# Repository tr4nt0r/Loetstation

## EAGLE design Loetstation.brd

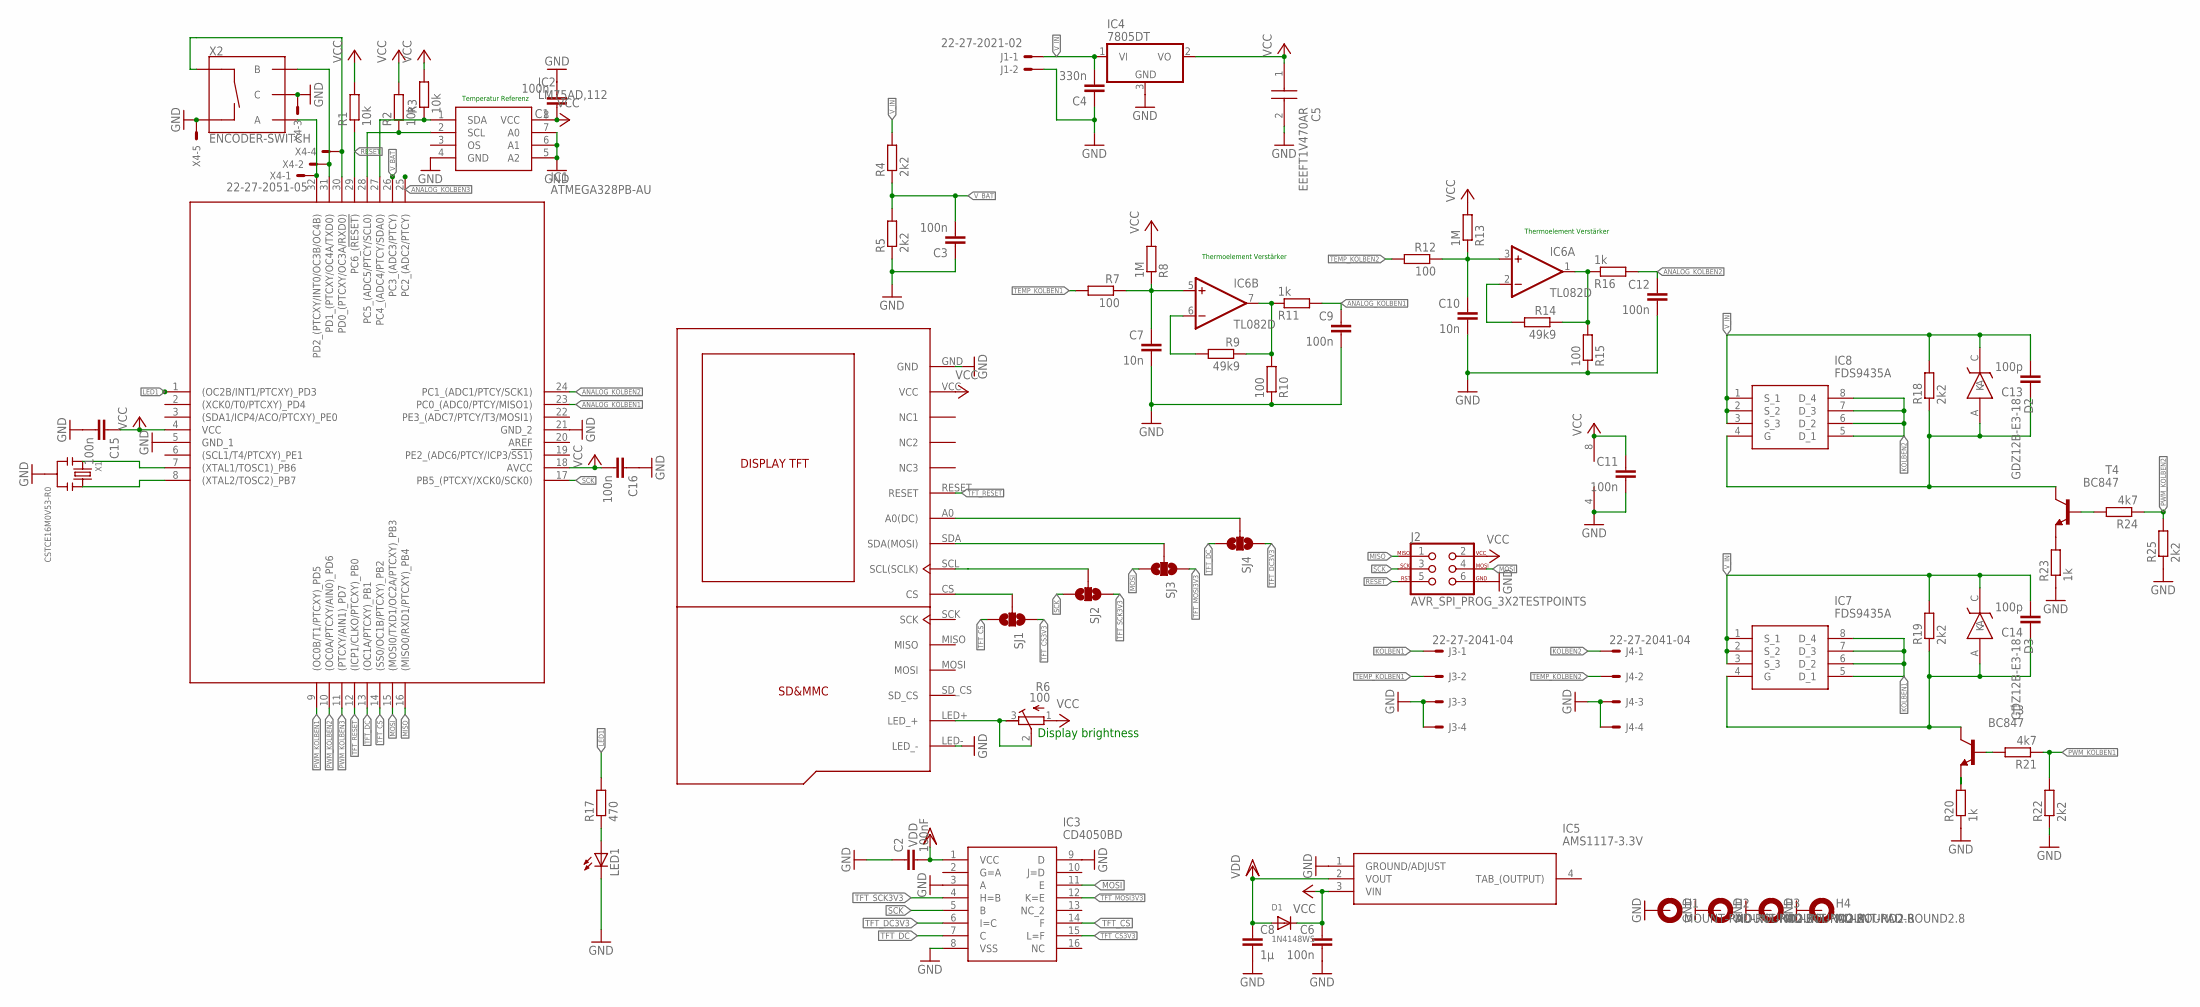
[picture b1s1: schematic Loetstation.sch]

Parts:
C1, C3, C6, C9, C11, C12, C15, C16: 100n; C0603
C2: 100nF; C0603
C4: 330n; C0603
C5: EEEFT1V470AR; EEEFT(C)
C7, C10: 10n; C0603
C8: 1µ; C0603
C13, C14: 100p; C0603
D1: 1N4148WS; SOD-323F
D2, D3: GDZ12B-E3-18; SOD323-W
H1, H2, H3, H4: MOUNT-PAD-ROUND2.8; 2,8-PAD
IC1: ATMEGA328PB-AU; QFP80P900X900X120-32N
IC2: LM75AD,112; SOIC127P600X175-8N
IC3: CD4050BD; SOIC127P600X175-16N
IC4: 7805DT; TO252
IC5: AMS1117-3.3V; SOT229P700X180-4N
IC6: TL082D; SO08
IC7, IC8: FDS9435A; SOIC127P600X175-8N
J1: 22-27-2021-02; 6410-02
J2: AVR_SPI_PROG_3X2TESTPOINTS; 2X3_TEST_POINTS
J3, J4: 22-27-2041-04; 6410-04
LED1: LEDCHIPLED_0805; CHIPLED_0805
R1, R2, R3: 10k; R0402
R4, R5, R18, R19, R22, R25: 2k2; R0402
R6: 100; EVM-3ESX50B
R7, R10, R12, R15: 100; R0402
R8, R13: 1M; R0402
R9, R14: 49k9; R0402
R11, R16, R20, R23: 1k; R0402
R17: 470; R0402
R21, R24: 4k7; R0402
SJ1, SJ2, SJ3, SJ4: SOLDERJUMPER_2WAYS; SJ_3
T3, T4: BC847; SOT23
X1: CSTCE16M0V53-R0; CSTCE-V
X3: DISPLAY_TFT_1,8; DISPLAY_TFT_1,8-KMR
X4: 22-27-2051-05; 6410-05

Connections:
ANALOG_KOLBEN1: C9.1, IC1.23 (PC0_(ADC0/PTCY/MISO1)), R11.2
ANALOG_KOLBEN2: C12.1, IC1.24 (PC1_(ADC1/PTCY/SCK1)), R16.2
ANALOG_KOLBEN3: IC1.25 (PC2_(ADC2/PTCY))
GND: C1.2, C2.1, C3.1, C4.1, C5.2 (+), C6.2, C7.2, C8.2, C9.2, C10.2, C11.2, C12.2, C15.2, C16.1, H1.B2,8, H2.B2,8, H3.B2,8, H4.B2,8, IC1.5 (GND_1), IC1.21 (GND_2), IC2.4 (GND), IC2.5 (A2), IC2.6 (A1), IC2.7 (A0), IC3.3 (A), IC3.8 (VSS), IC3.9 (D), IC4.3 (GND), IC5.1 (GROUND/ADJUST), IC6.4 (V-), J1.2, J2.6, J3.3, J3.4, J4.3, J4.4, LED1.C, R5.1, R10.1, R15.1, R20.1, R22.1, R23.1, R25.1, X1.2, X3.GND, X3.LED- (LED_-), X4.3, X4.5
KOLBEN1: IC7.5 (D_1), IC7.6 (D_2), IC7.7 (D_3), IC7.8 (D_4), J3.1
KOLBEN2: IC8.5 (D_1), IC8.6 (D_2), IC8.7 (D_3), IC8.8 (D_4), J4.1
LED1: IC1.1 ((OC2B/INT1/PTCXY)_PD3), R17.2
MISO: IC1.16 ((MISO0/RXD1/PTCXY)_PB4), J2.1
MOSI: IC1.15 ((MOSI0/TXD1/OC2A/PTCXY)_PB3), IC3.11 (E), J2.4, SJ3.3
unnamed: SJ4.2, X3.A0 (A0(DC))
unnamed: SJ3.2, X3.SDA (SDA(MOSI))
unnamed: C13.1, D2.A, IC8.4 (G), R18.1, T4.3 (C)
unnamed: C14.1, D3.A, IC7.4 (G), R19.1, T3.3 (C)
unnamed: R24.2, T4.1 (B)
unnamed: R23.2, T4.2 (E)
unnamed: IC6.7 (OUT), R9.1, R10.2, R11.1
unnamed: R21.2, T3.1 (B)
unnamed: R20.2, T3.2 (E)
unnamed: C7.1, IC6.5 (+IN), R7.1, R8.1
unnamed: IC1.7 ((XTAL1/TOSC1)_PB6), X1.1
unnamed: IC1.8 ((XTAL2/TOSC2)_PB7), X1.3
unnamed: IC1.28 (PC5_(ADC5/PTCY/SCL0)), IC2.2 (SCL), R2.1
unnamed: IC1.27 (PC4_(ADC4/PTCY/SDA0)), IC2.1 (SDA), R3.1
unnamed: SJ2.2, X3.SCL (SCL(SCLK))
unnamed: SJ1.2, X3.CS
unnamed: IC6.6 (-IN), R9.2
unnamed: C10.1, IC6.3 (+IN), R12.1, R13.1
unnamed: LED1.A, R17.1
unnamed: IC1.32 (PD2_(PTCXY/INT0/OC3B/OC4B)), X4.1
unnamed: IC1.31 (PD1_(PTCXY/OC4A/TXD0)), X4.2
unnamed: IC1.30 (PD0_(PTCXY/OC3A/RXD0)), X4.4
unnamed: R6.2 (S), R6.3 (E), X3.LED+ (LED_+)
unnamed: IC6.1 (OUT), R14.1, R15.2, R16.1
unnamed: IC6.2 (-IN), R14.2
PWM_KOLBEN1: IC1.9 ((OC0B/T1/PTCXY)_PD5), R21.1, R22.2
PWM_KOLBEN2: IC1.10 ((OC0A/PTCXY/AIN0)_PD6), R24.1, R25.2
PWM_KOLBEN3: IC1.11 ((PTCXY/AIN1)_PD7)
RESET: IC1.29 (PC6_(!RESET)), J2.5, R1.1
SCK: IC1.17 (PB5_(PTCXY/XCK0/SCK0)), IC3.5 (B), J2.3, SJ2.3
TEMP_KOLBEN1: J3.2, R7.2
TEMP_KOLBEN2: J4.2, R12.2
TFT_CS: IC1.14 ((SS0/OC1B/PTCXY)_PB2), IC3.14 (F), SJ1.3
TFT_CS3V3: IC3.15 (L=F), SJ1.1
TFT_DC: IC1.13 ((OC1A/PTCXY)_PB1), IC3.7 (C), SJ4.3
TFT_DC3V3: IC3.6 (I=C), SJ4.1
TFT_MOSI3V3: IC3.12 (K=E), SJ3.1
TFT_RESET: IC1.12 ((ICP1/CLKO/PTCXY)_PB0), X3.RESET
TFT_SCK3V3: IC3.4 (H=B), SJ2.1
VCC: C1.1, C5.1 (-), C6.1, C11.1, C15.1, C16.2, D1.C, IC1.4 (VCC), IC1.18 (AVCC), IC2.8 (VCC), IC4.2 (VO), IC5.3 (VIN), IC6.8 (V+), J2.2, R1.2, R2.2, R3.2, R6.1 (A), R8.2, R13.2, X3.VCC
VDD: C2.2, C8.1, D1.A, IC3.1 (VCC), IC5.2 (VOUT)
V_BAT: C3.2, IC1.26 (PC3_(ADC3/PTCY)), R4.1, R5.2
V_IN: C4.2, C13.2, C14.2, D2.C (K), D3.C (K), IC4.1 (VI), IC7.1 (S_1), IC7.2 (S_2), IC7.3 (S_3), IC8.1 (S_1), IC8.2 (S_2), IC8.3 (S_3), J1.1, R4.2, R18.2, R19.2

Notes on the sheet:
Display brightness
Temperatur Referenz
Thermoelement Verstärker

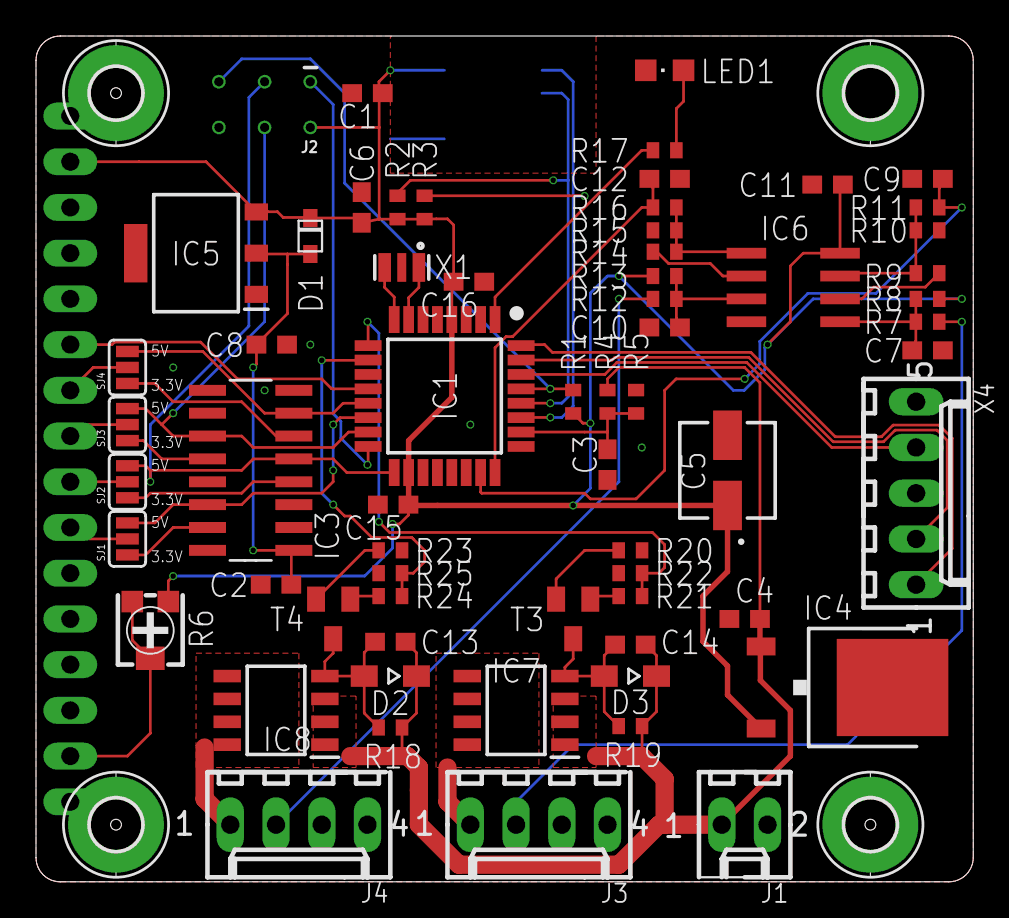
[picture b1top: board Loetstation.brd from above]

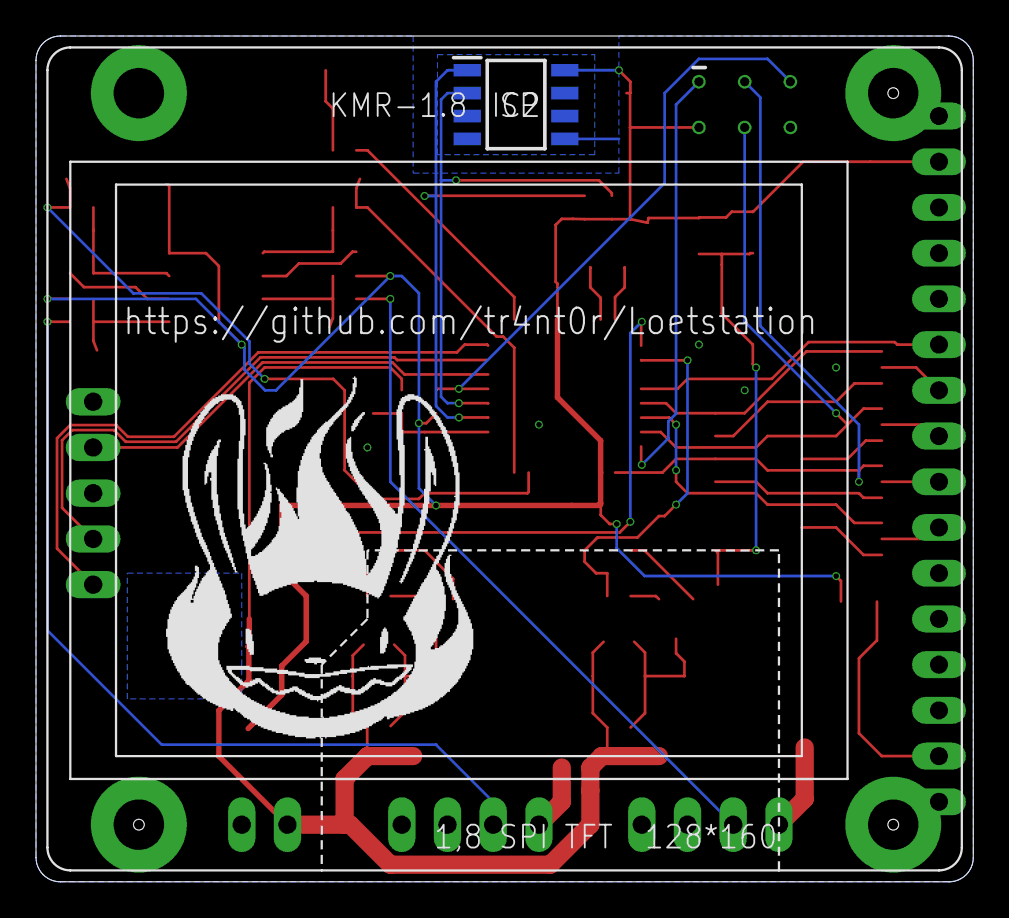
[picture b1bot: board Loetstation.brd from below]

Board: 2 copper layers, 52.1 x 47.0 mm, 70 parts (2 on the bottom side), 50 nets.

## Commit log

2018-10-06 added Github URL to Board
2018-10-06 moved text position
2018-10-06 pcb images
2018-10-06 changed capacitor package from 0402 to 0603
2018-12-11 Power-MOSFETs durch FDS9435A getauscht
2018-12-15 Abblock Kondensatoren für µC hinzugefügt

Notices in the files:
parts and their libraries:
SparkFun-Retired: Licensing: Creative Commons ShareAlike 4.0 International - https://creativecommons.org/licenses/by-sa/4.0
